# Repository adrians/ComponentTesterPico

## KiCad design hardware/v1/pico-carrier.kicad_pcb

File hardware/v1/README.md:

# Component tester HW - v1

Use the `panelisation.sh` script to generate 1x2 PCB panels.

The script uses kikit. To install kikit run `pip3 install kikit`.

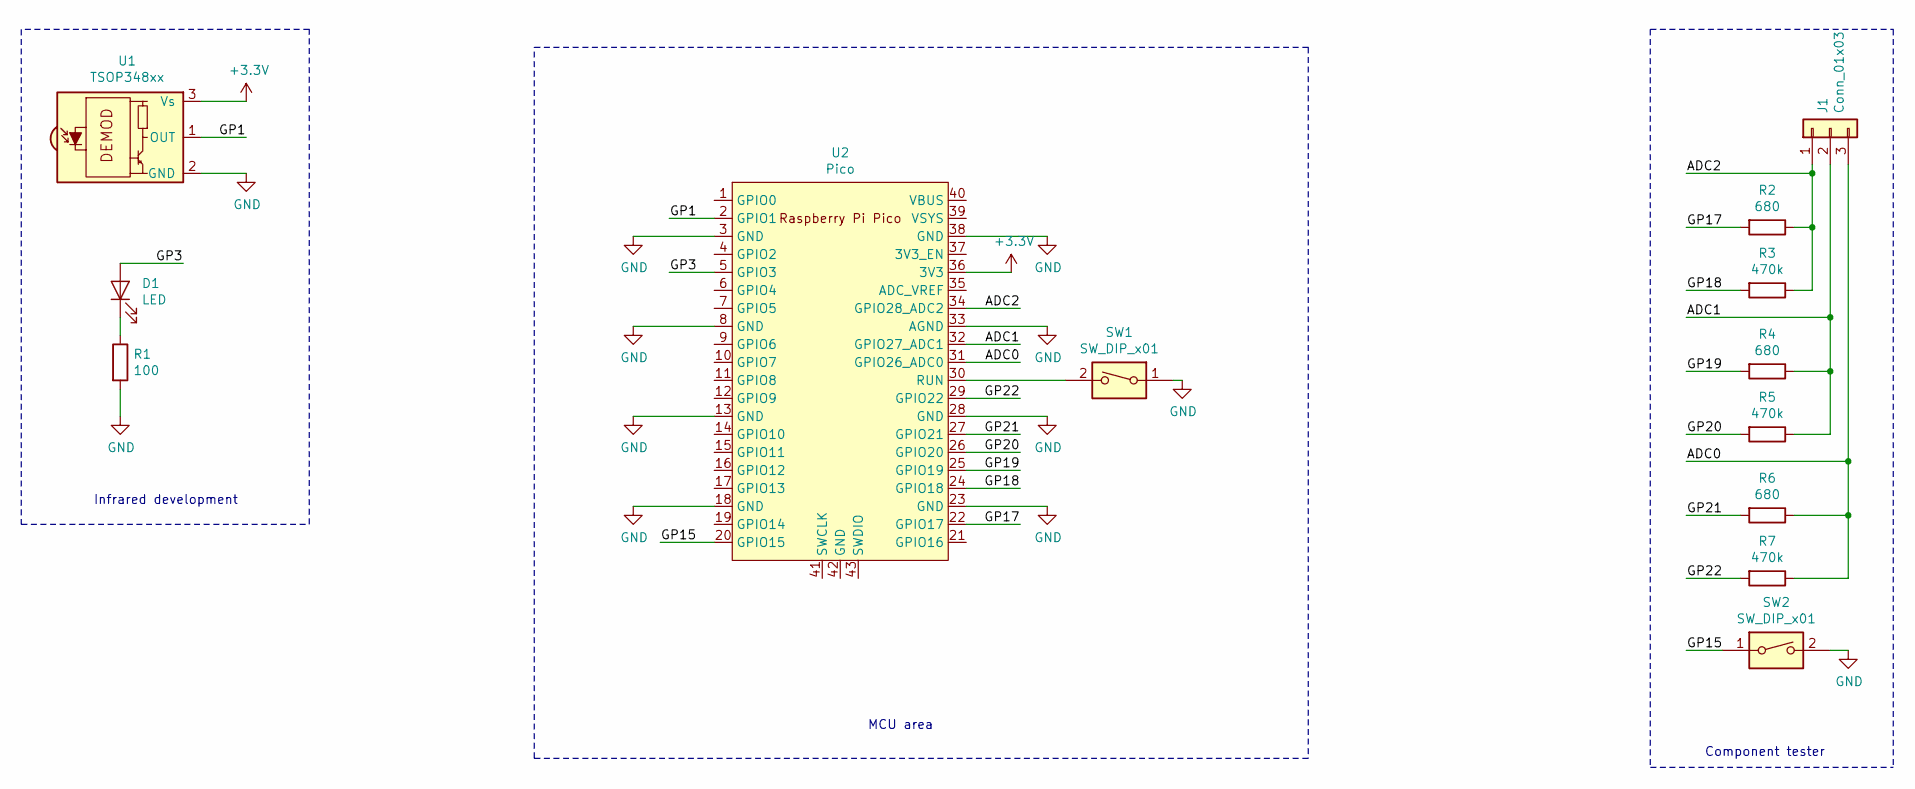
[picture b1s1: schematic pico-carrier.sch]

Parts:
D1: LED; LED_D5.0mm
J1: Conn_01x03; PinHeader_1x03_P2.54mm_Vertical
R1: 100; R_0805_2012Metric_Pad1.15x1.40mm_HandSolder
R2, R4, R6: 680; R_0805_2012Metric_Pad1.15x1.40mm_HandSolder
R3, R5, R7: 470k; R_0805_2012Metric_Pad1.15x1.40mm_HandSolder
SW1, SW2: SW_DIP_x01; SW_PUSH_6mm
U1: TSOP348xx; Vishay_MOLD-3Pin
U2: Pico; RPi_Pico_SMD_TH

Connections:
+3V3: U1.3 (Vs), U2.36 (3V3)
/ADC0: J1.3, R6.1, R7.1, U2.31 (GPIO26_ADC0)
/ADC1: J1.2, R4.1, R5.1, U2.32 (GPIO27_ADC1)
/ADC2: J1.1, R2.1, R3.1, U2.34 (GPIO28_ADC2)
/GP1: U1.1 (OUT), U2.2 (GPIO1)
/GP3: D1.2 (A), U2.5 (GPIO3)
/GP15: SW2.1, U2.20 (GPIO15)
/GP17: R2.2, U2.22 (GPIO17)
/GP18: R3.2, U2.24 (GPIO18)
/GP19: R4.2, U2.25 (GPIO19)
/GP20: R5.2, U2.26 (GPIO20)
/GP21: R6.2, U2.27 (GPIO21)
/GP22: R7.2, U2.29 (GPIO22)
GND: R1.2, SW1.1, SW2.2, U1.2 (GND), U2.3 (GND), U2.8 (GND), U2.13 (GND), U2.18 (GND), U2.23 (GND), U2.28 (GND), U2.33 (AGND), U2.38 (GND)
unnamed: D1.1 (K), R1.1
unnamed: SW1.2, U2.30 (RUN)

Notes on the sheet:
Component tester
Infrared development
MCU area

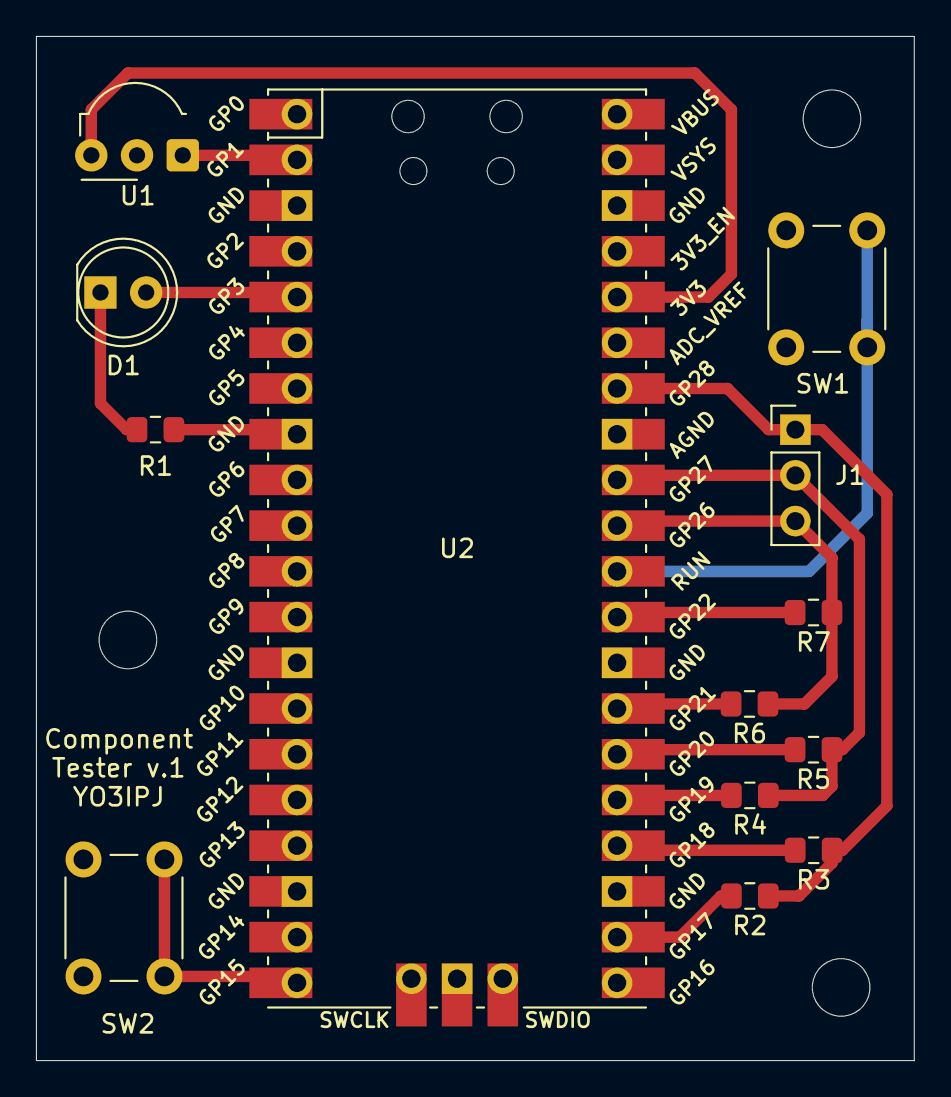
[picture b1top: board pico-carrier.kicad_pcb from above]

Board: 2 copper layers, 48.8 x 56.9 mm, 13 parts (0 on the bottom side), 16 nets.

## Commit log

2022-06-22 hardware/v1: add readme
2022-07-06 software/v1: setup project
2022-07-08 software/v1: add resistor measurement
2022-08-16 v1-bmp280-wifi: add code for project
2022-08-16 v1: add code for NEC receive & transmit
2022-08-16 v1: add work-in-progress NEC transmit draft
